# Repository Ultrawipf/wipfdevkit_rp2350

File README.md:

## DM 14 Wipf

### Requirements:

* [Circuitpython](https://circuitpython.org/board/raspberry_pi_pico2/)
* Circuitpython [library bundle](https://circuitpython.org/libraries)

### Features
* RP2350 (Raspberry pi pico 2)
* 16MB Flash
* 520kB ram
* Dual core ARM + RiscV
* FS USB

#### Functions
* 18 WS2812 leds: GP8
* [MMA8451](https://www.lcsc.com/product-detail/C118083.html) Accelerometer : I2C GP 2/3
* [Buzzer](https://www.lcsc.com/product-detail/C18623826.html) (Beep,Boop,Snuff) : GP1
* 8 Buttons
* [Circuitpython](https://docs.circuitpython.org/en/latest/README.html)

#### Demoprogram
* HID Clonk keyboard mode
* Accelerometer demo
* Buzzer demo
* Disco lights
* Async python

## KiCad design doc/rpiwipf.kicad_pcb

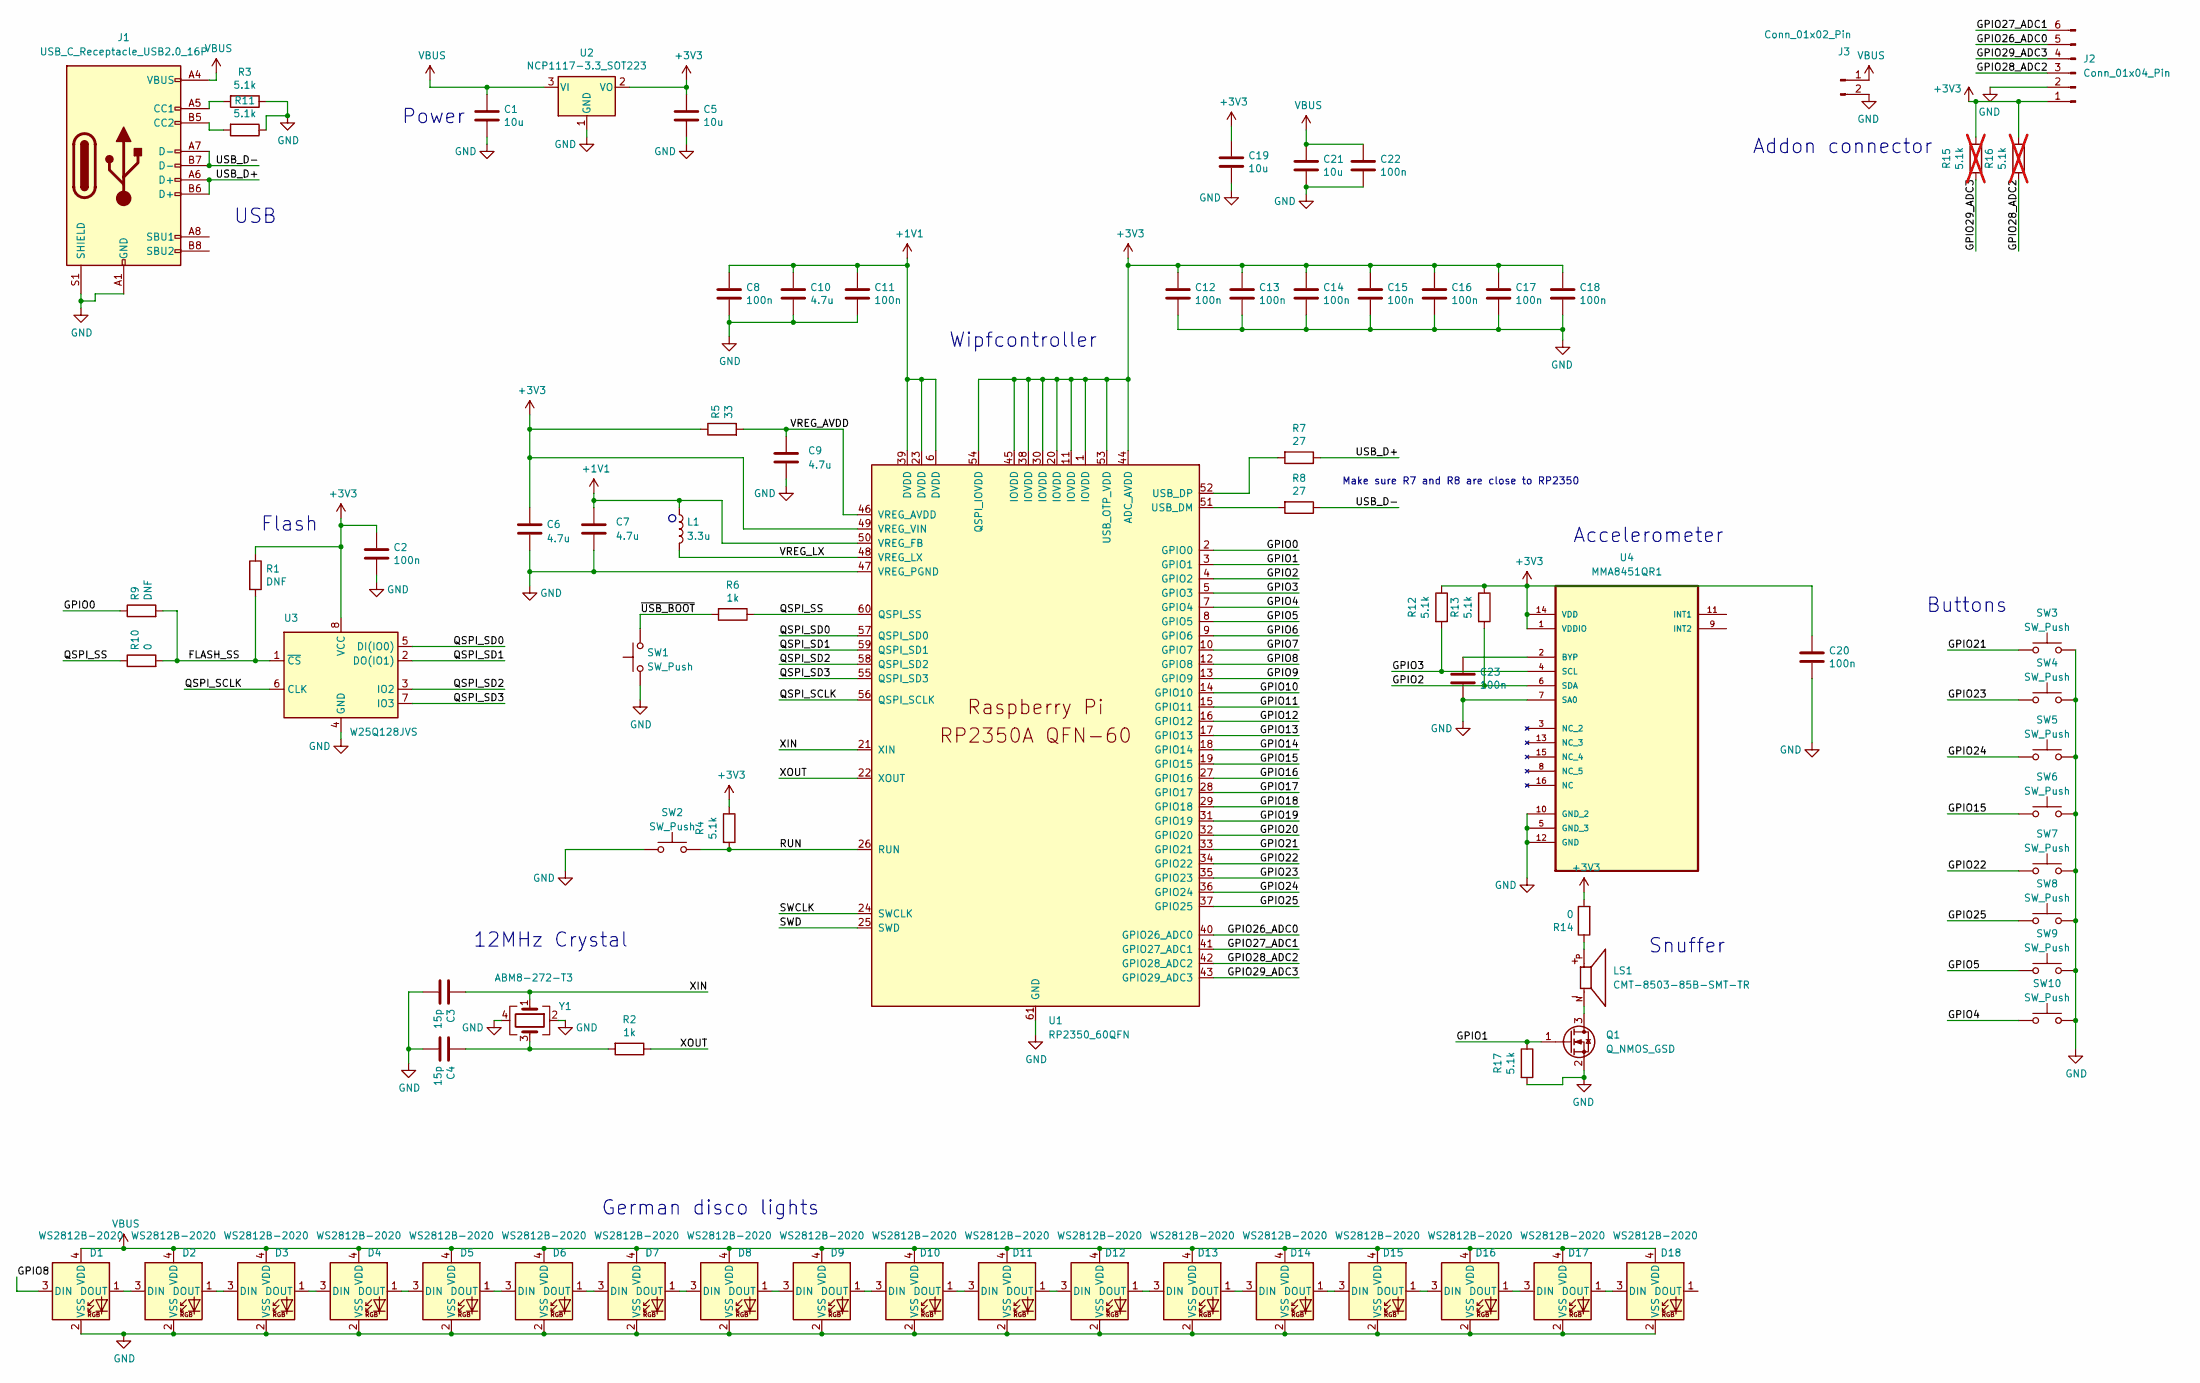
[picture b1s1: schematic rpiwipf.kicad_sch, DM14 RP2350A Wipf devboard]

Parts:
C1, C5, C19, C21: 10u; C_0805_2012Metric
C2, C8, C11, C12, C13, C14, C15, C16, C17, C18, C20, C22, C23: 100n; C_0603_1608Metric
C3, C4: 15p; C_0603_1608Metric
C6, C7, C9, C10: 4.7u; C_0603_1608Metric
D1, D2, D3, D4, D5, D6, D7, D8, D9, D10, D11, D12, D13, D14, D15, D16, D17, D18: WS2812B-2020; LED_WS2812B-2020_PLCC4_2.0x2.0mm
J1: USB_C_Receptacle_USB2.0_16P; USB_C_Receptacle_XKB_U262-16XN-4BVC11
J2: Conn_01x04_Pin; PinHeader_2x03_P2.54mm_Vertical
J3: Conn_01x02_Pin; PinHeader_1x02_P2.54mm_Vertical
L1: 3.3u; L_pol_2016
LS1: CMT-8503-85B-SMT-TR; XDCR_CMT-8503-85B-SMT-TR; PARTREV 1.0
Q1: Q_NMOS_GSD; SOT-23-3
R1, R9: DNF; R_0603_1608Metric
R2, R6: 1k; R_0603_1608Metric
R3, R4, R11, R12, R13, R17: 5.1k; R_0603_1608Metric
R5: 33; R_0603_1608Metric
R7, R8: 27; R_0603_1608Metric
R10, R14: 0; R_0603_1608Metric
R15, R16: 5.1k; R_0603_1608Metric; not fitted
SW1, SW2, SW3, SW4, SW5, SW6, SW7, SW8, SW9, SW10: SW_Push; SW_SPST_SKQG_WithoutStem
U1: RP2350_60QFN; RP2350-QFN-60-1EP_7x7_P0.4mm_EP3.4x3.4mm_ThermalVias
U2: NCP1117-3.3_SOT223; SOT-223-3_TabPin2
U3: W25Q128JVS; SOIC-8_5.23x5.23mm_P1.27mm
U4: MMA8451QR1; QFN50P300X300X100-16N; MPN MMA8451QR1
Y1: ABM8-272-T3; Crystal_SMD_3225-4Pin_3.2x2.5mm

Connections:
+1V1: C7.1, C8.1, C10.1, C11.1, L1.1, U1.6 (DVDD), U1.23 (DVDD), U1.39 (DVDD), U1.50 (VREG_FB)
+3V3: C2.1, C5.1, C6.1, C12.1, C13.1, C14.1, C15.1, C16.1, C17.1, C18.1, C19.1, C20.1, J2.1, R1.1, R4.1, R5.1, R12.1, R13.1, R14.2, R15.1, R16.1, U1.1 (IOVDD), U1.11 (IOVDD), U1.20 (IOVDD), U1.30 (IOVDD), U1.38 (IOVDD), U1.44 (ADC_AVDD), U1.45 (IOVDD), U1.49 (VREG_VIN), U1.53 (USB_OTP_VDD), U1.54 (QSPI_IOVDD), U2.2 (VO), U3.8 (VCC), U4.1 (VDDIO), U4.14 (VDD)
/FLASH_SS: R1.2, R9.2, R10.2, U3.1 (~CS)
/GPIO0: R9.1, U1.2 (GPIO0)
/GPIO1: Q1.1 (G), R17.1, U1.3 (GPIO1)
/GPIO2: R13.2, U1.4 (GPIO2), U4.6 (SDA)
/GPIO3: R12.2, U1.5 (GPIO3), U4.4 (SCL)
/GPIO4: SW10.1, U1.7 (GPIO4)
/GPIO5: SW9.1, U1.8 (GPIO5)
/GPIO6: U1.9 (GPIO6)
/GPIO7: U1.10 (GPIO7)
/GPIO8: D1.3 (DIN), U1.12 (GPIO8)
/GPIO9: U1.13 (GPIO9)
/GPIO10: U1.14 (GPIO10)
/GPIO11: U1.15 (GPIO11)
/GPIO12: U1.16 (GPIO12)
/GPIO13: U1.17 (GPIO13)
/GPIO14: U1.18 (GPIO14)
/GPIO15: SW6.1, U1.19 (GPIO15)
/GPIO16: U1.27 (GPIO16)
/GPIO17: U1.28 (GPIO17)
/GPIO18: U1.29 (GPIO18)
/GPIO19: U1.31 (GPIO19)
/GPIO20: U1.32 (GPIO20)
/GPIO21: SW3.1, U1.33 (GPIO21)
/GPIO22: SW7.1, U1.34 (GPIO22)
/GPIO23: SW4.1, U1.35 (GPIO23)
/GPIO24: SW5.1, U1.36 (GPIO24)
/GPIO25: SW8.1, U1.37 (GPIO25)
/GPIO26_ADC0: J2.5, U1.40 (GPIO26_ADC0)
/GPIO27_ADC1: J2.6, U1.41 (GPIO27_ADC1)
/GPIO28_ADC2: J2.3, R16.2, U1.42 (GPIO28_ADC2)
/GPIO29_ADC3: J2.4, R15.2, U1.43 (GPIO29_ADC3)
/QSPI_SCLK: U1.56 (QSPI_SCLK), U3.6 (CLK)
/QSPI_SD0: U1.57 (QSPI_SD0), U3.5 (DI(IO0))
/QSPI_SD1: U1.59 (QSPI_SD1), U3.2 (DO(IO1))
/QSPI_SD2: U1.58 (QSPI_SD2), U3.3 (IO2)
/QSPI_SD3: U1.55 (QSPI_SD3), U3.7 (IO3)
/QSPI_SS: R6.1, R10.1, U1.60 (QSPI_SS)
/RUN: R4.2, SW2.2, U1.26 (RUN)
/SWCLK: U1.24 (SWCLK)
/SWD: U1.25 (SWD)
/USB_D+: J1.A6 (D+), J1.B6 (D+), R7.1
/USB_D-: J1.A7 (D-), J1.B7 (D-), R8.1
/VREG_AVDD: C9.1, R5.2, U1.46 (VREG_AVDD)
/VREG_LX: L1.2, U1.48 (VREG_LX)
/XIN: C3.1, U1.21 (XIN), Y1.1
/XOUT: R2.1, U1.22 (XOUT)
/~USB_BOOT: R6.2, SW1.2
GND: C1.2, C2.2, C3.2, C4.2, C5.2, C6.2, C7.2, C8.2, C9.2, C10.2, C11.2, C12.2, C13.2, C14.2, C15.2, C16.2, C17.2, C18.2, C19.2, C20.2, C21.2, C22.2, C23.2, D1.2 (VSS), D2.2 (VSS), D3.2 (VSS), D4.2 (VSS), D5.2 (VSS), D6.2 (VSS), D7.2 (VSS), D8.2 (VSS), D9.2 (VSS), D10.2 (VSS), D11.2 (VSS), D12.2 (VSS), D13.2 (VSS), D14.2 (VSS), D15.2 (VSS), D16.2 (VSS), D17.2 (VSS), D18.2 (VSS), J1.A1 (GND), J1.A12 (GND), J1.B1 (GND), J1.B12 (GND), J1.S1 (SHIELD), J2.2, J3.2, Q1.2 (S), R3.1, R11.1, R17.2, SW1.1, SW2.1, SW3.2, SW4.2, SW5.2, SW6.2, SW7.2, SW8.2, SW9.2, SW10.2, U1.47 (VREG_PGND), U1.61 (GND), U2.1 (GND), U3.4 (GND), U4.5 (GND_3), U4.7 (SA0), U4.10 (GND_2), U4.12 (GND), Y1.2, Y1.4
unnamed: C4.1, R2.2, Y1.3
unnamed: D1.1 (DOUT), D2.3 (DIN)
unnamed: D2.1 (DOUT), D3.3 (DIN)
unnamed: D3.1 (DOUT), D4.3 (DIN)
unnamed: D4.1 (DOUT), D5.3 (DIN)
unnamed: D5.1 (DOUT), D6.3 (DIN)
unnamed: D6.1 (DOUT), D7.3 (DIN)
unnamed: D7.1 (DOUT), D8.3 (DIN)
unnamed: D8.1 (DOUT), D9.3 (DIN)
unnamed: D9.1 (DOUT), D10.3 (DIN)
unnamed: D10.1 (DOUT), D11.3 (DIN)
unnamed: D11.1 (DOUT), D12.3 (DIN)
unnamed: D12.1 (DOUT), D13.3 (DIN)
unnamed: D13.1 (DOUT), D14.3 (DIN)
unnamed: D14.1 (DOUT), D15.3 (DIN)
unnamed: D15.1 (DOUT), D16.3 (DIN)
unnamed: D16.1 (DOUT), D17.3 (DIN)
unnamed: D17.1 (DOUT), D18.3 (DIN)
unnamed: J1.A5 (CC1), R3.2
unnamed: J1.B5 (CC2), R11.2
unnamed: LS1.P, R14.1
unnamed: LS1.N, Q1.3 (D)
unnamed: R8.2, U1.51 (USB_DM)
unnamed: R7.2, U1.52 (USB_DP)
unnamed: C23.1, U4.2 (BYP)
VBUS: C1.1, C21.1, C22.1, D1.4 (VDD), D2.4 (VDD), D3.4 (VDD), D4.4 (VDD), D5.4 (VDD), D6.4 (VDD), D7.4 (VDD), D8.4 (VDD), D9.4 (VDD), D10.4 (VDD), D11.4 (VDD), D12.4 (VDD), D13.4 (VDD), D14.4 (VDD), D15.4 (VDD), D16.4 (VDD), D17.4 (VDD), D18.4 (VDD), J1.A4 (VBUS), J1.A9 (VBUS), J1.B4 (VBUS), J1.B9 (VBUS), J3.1, U2.3 (VI)

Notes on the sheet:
Snuffer
Flash
Wipfcontroller
Make sure R7 and R8 are close to RP2350
USB
Addon connector
Buttons
German disco lights
12MHz Crystal
Power
Accelerometer

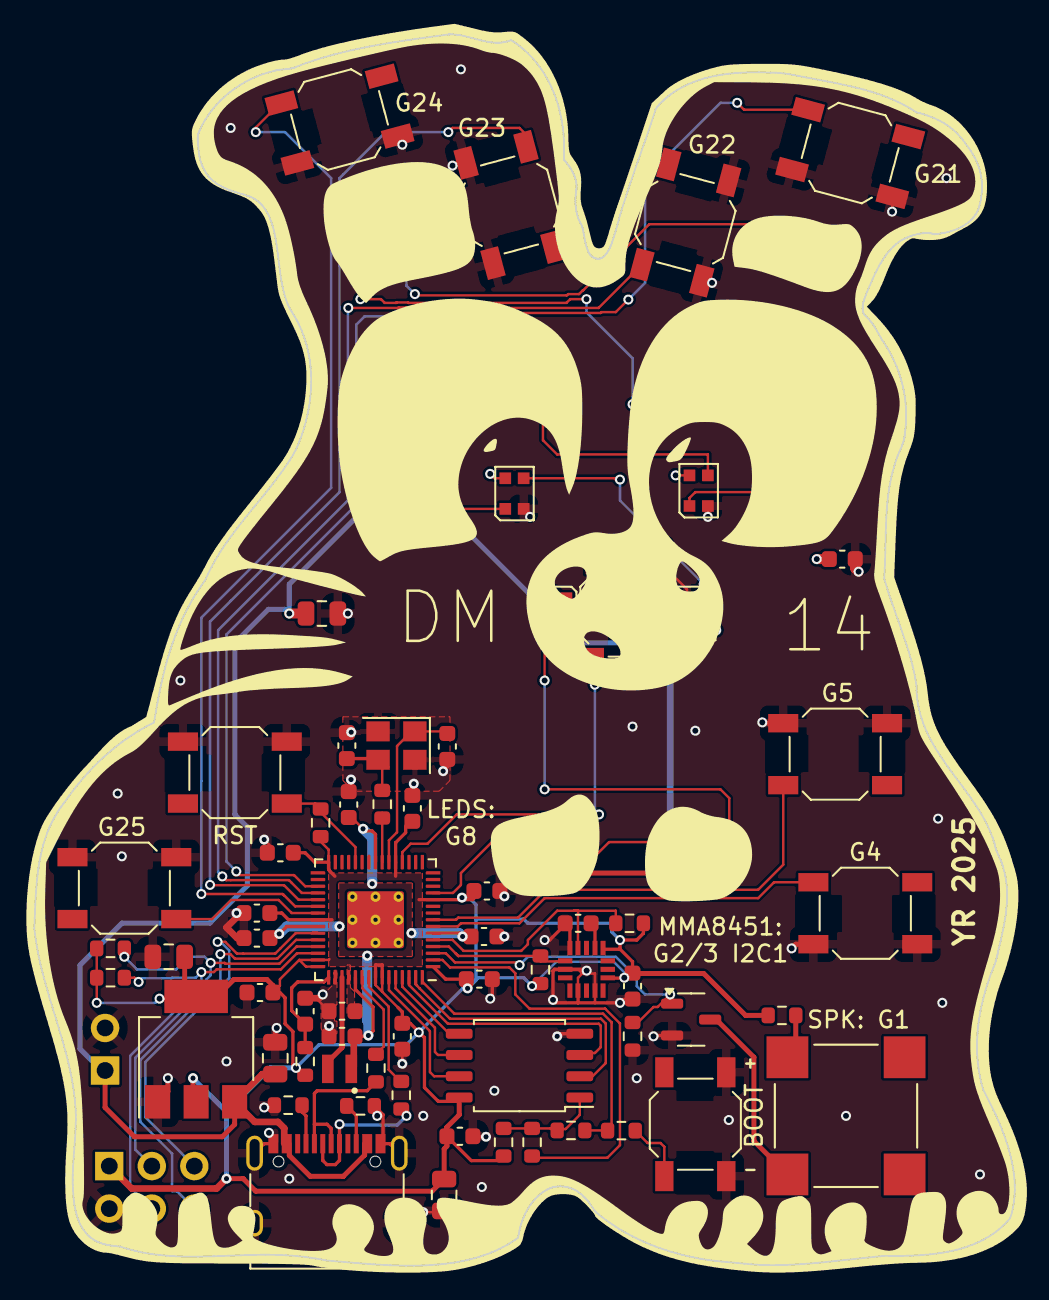
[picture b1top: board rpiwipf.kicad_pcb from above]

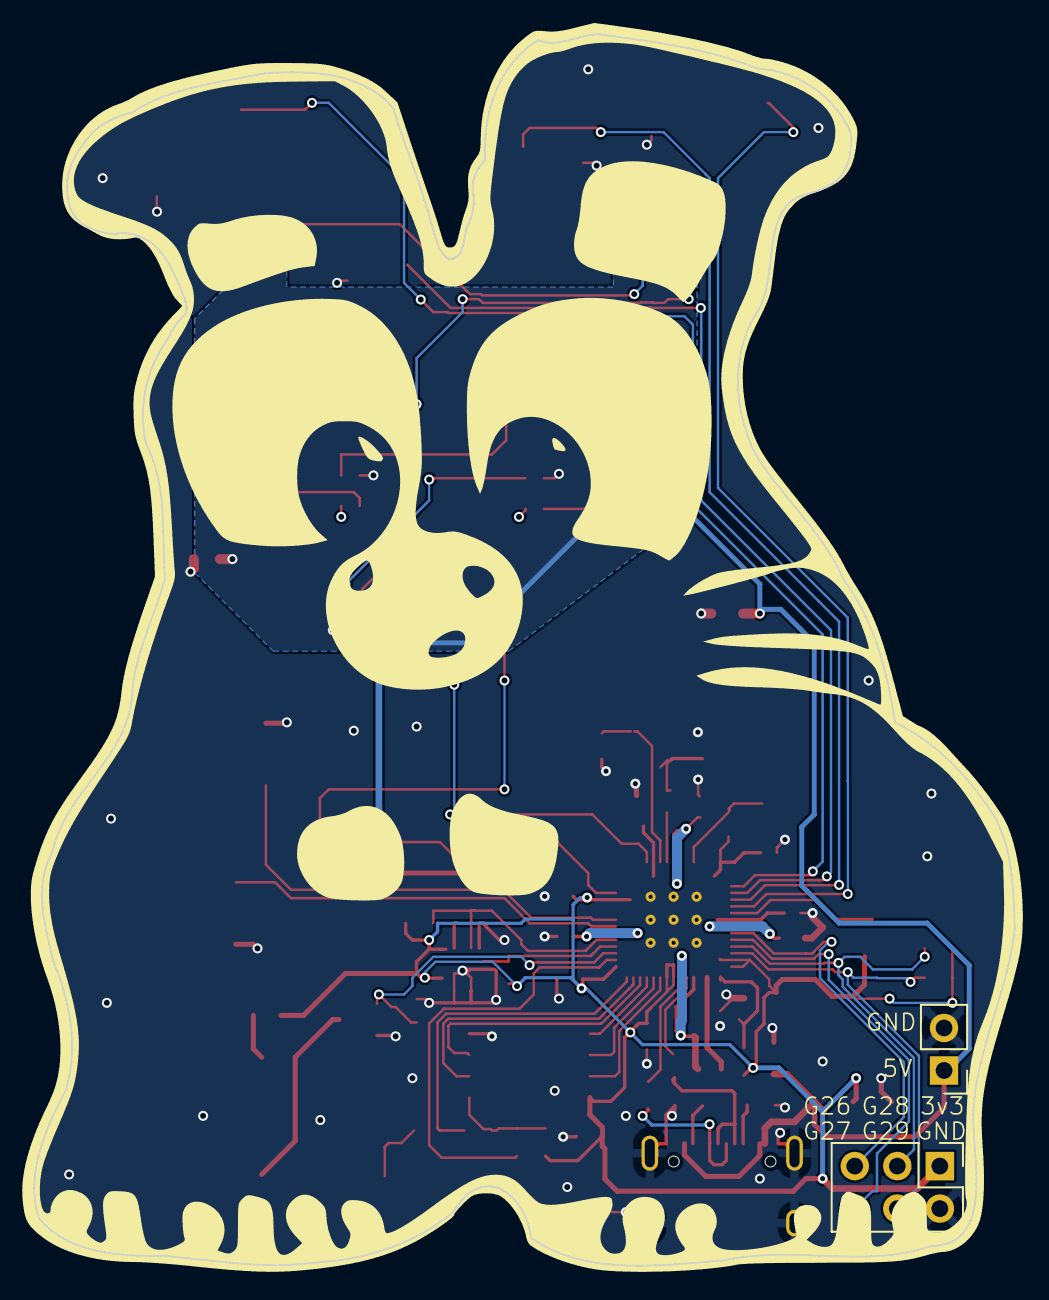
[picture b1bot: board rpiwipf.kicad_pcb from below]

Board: 2 copper layers, 58.6 x 73.5 mm, 79 parts (2 on the bottom side), 61 nets.

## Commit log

2025-09-11 Detect usb state
2025-09-14 Update accelerometer lib
2025-09-14 Update acc
